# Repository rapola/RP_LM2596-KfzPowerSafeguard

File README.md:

# RP_LM2596-KfzPowerSafeguard

<br>
### Schematic
#### https://github.com/rapola/RP_LM2596-KfzPowerSafeguard/blob/main/V1.0/RP_LM2596-KfzPowerSafeguard.pdf
---
#### not ordered yet
---
#### take care, differen LM2596-Modules on ebay!! Difference in Mounting Holes!!

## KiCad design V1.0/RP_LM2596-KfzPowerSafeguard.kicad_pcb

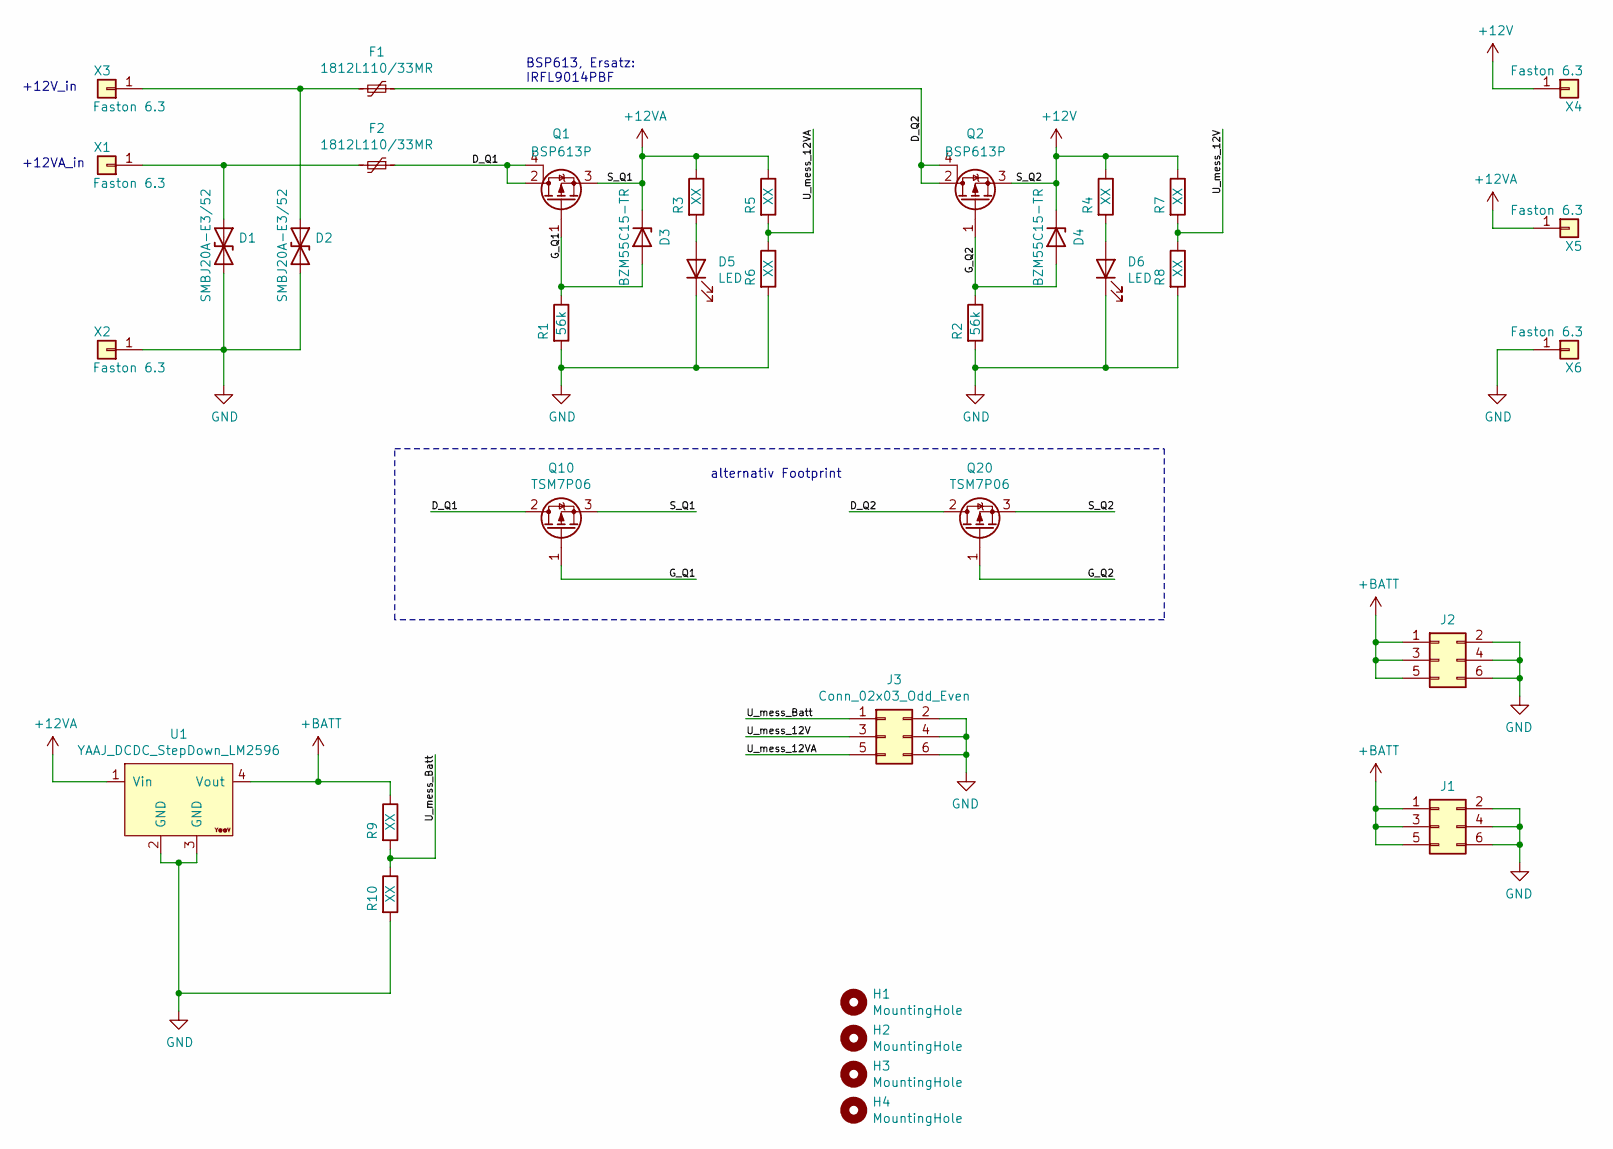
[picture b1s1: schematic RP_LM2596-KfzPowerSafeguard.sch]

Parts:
D1, D2: SMBJ20A-E3/52; D_SMB
D3, D4: BZM55C15-TR; D_MicroMELF
D5, D6: LED; LED_0805_2012Metric
F1, F2: 1812L110/33MR; R_1812_4532Metric
H1, H2, H3, H4: MountingHole; MountingHole_3.2mm_M3
J1, J2, J3: Conn_02x03_Odd_Even; PinHeader_2x03_P2.54mm_Horizontal
Q1, Q2: BSP613P; SOT-223
Q10, Q20: TSM7P06; TO-252-2
R1, R2: 56k; R_0805_2012Metric
R3, R4, R5, R6, R7, R8, R9, R10: XX; R_0805_2012Metric
U1: YAAJ_DCDC_StepDown_LM2596; YAAJ_DCDC_StepDown_LM2596_noSilk
X1, X2, X3, X4, X5, X6: Faston 6.3; Faston_1x_6,3-male-noSilk

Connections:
+12V: D4.1 (K), Q2.3 (S), Q20.3 (S), R4.1, R7.1, X4.1
+12VA: D3.1 (K), Q1.3 (S), Q10.3 (S), R3.1, R5.1, U1.1 (Vin), X5.1
+BATT: J1.1, J1.3, J1.5, J2.1, J2.3, J2.5, R9.1, U1.4 (Vout)
/D_Q1: F2.1, Q1.2 (D), Q1.4 (D), Q10.2 (D)
/D_Q2: F1.1, Q2.2 (D), Q2.4 (D), Q20.2 (D)
/G_Q1: D3.2 (A), Q1.1 (G), Q10.1 (G), R1.1
/G_Q2: D4.2 (A), Q2.1 (G), Q20.1 (G), R2.1
/U_mess_12V: J3.3, R7.2, R8.1
/U_mess_12VA: J3.5, R5.2, R6.1
/U_mess_Batt: J3.1, R9.2, R10.1
GND: D1.2 (A2), D2.2 (A2), D5.1 (K), D6.1 (K), J1.2, J1.4, J1.6, J2.2, J2.4, J2.6, J3.2, J3.4, J3.6, R1.2, R2.2, R6.2, R8.2, R10.2, U1.2 (GND), U1.3 (GND), X2.1, X6.1
unnamed: D1.1 (A1), F2.2, X1.1
unnamed: D2.1 (A1), F1.2, X3.1
unnamed: D5.2 (A), R3.2
unnamed: D6.2 (A), R4.2

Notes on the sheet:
+12VA_in
+12V_in
BSP613, Ersatz: IRFL9014PBF
alternativ Footprint

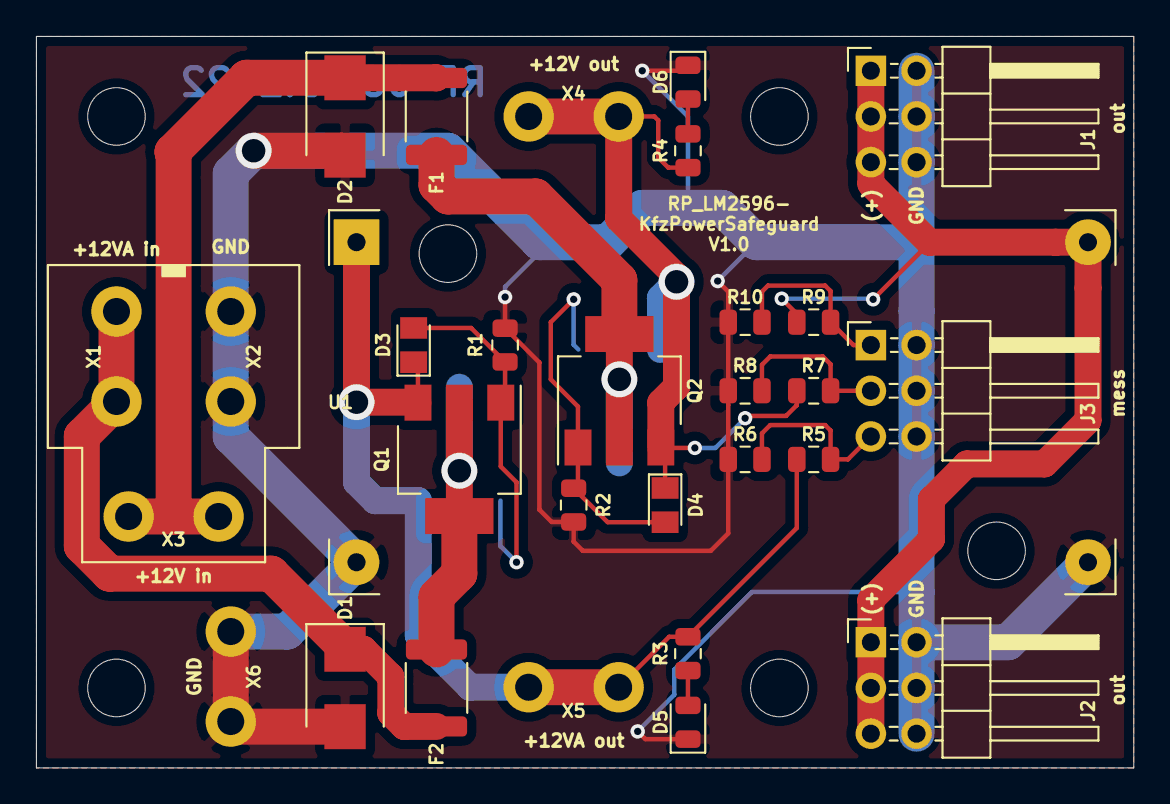
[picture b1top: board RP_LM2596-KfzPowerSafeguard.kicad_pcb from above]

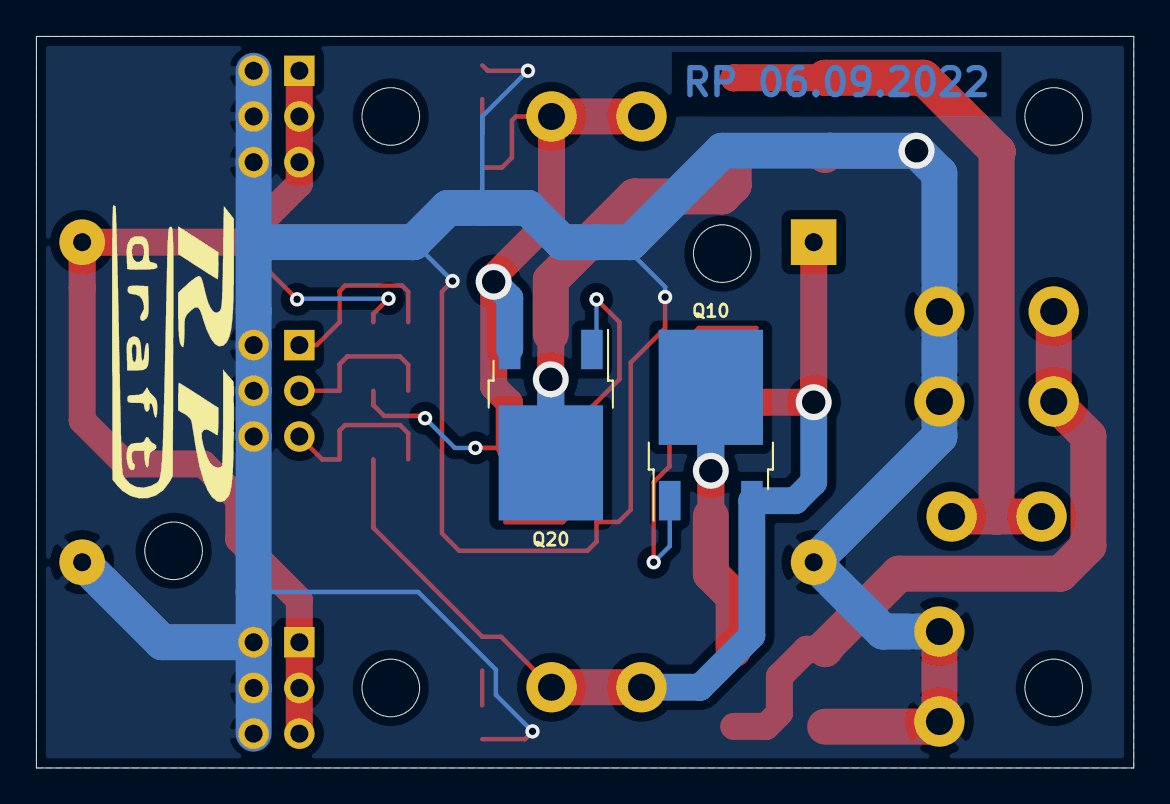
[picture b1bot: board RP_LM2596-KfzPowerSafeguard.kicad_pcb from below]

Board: 2 copper layers, 61.0 x 40.6 mm, 36 parts (2 on the bottom side), 15 nets.

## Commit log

2022-09-15 initial release
2022-09-15 updated pdf
2022-10-22 V1.0 Product datat generated
    10 pcs orderd at JLCPCB.com
2022-10-23 kicad library updated
